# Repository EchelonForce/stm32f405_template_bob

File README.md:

# SMT32F405RG Template/BOB

This is a design for a STM32F405 based breakout board.

This work is licensed under a Creative Commons Attribution-NonCommercial-ShareAlike 4.0 International License. https://creativecommons.org/licenses/by-nc-sa/4.0/

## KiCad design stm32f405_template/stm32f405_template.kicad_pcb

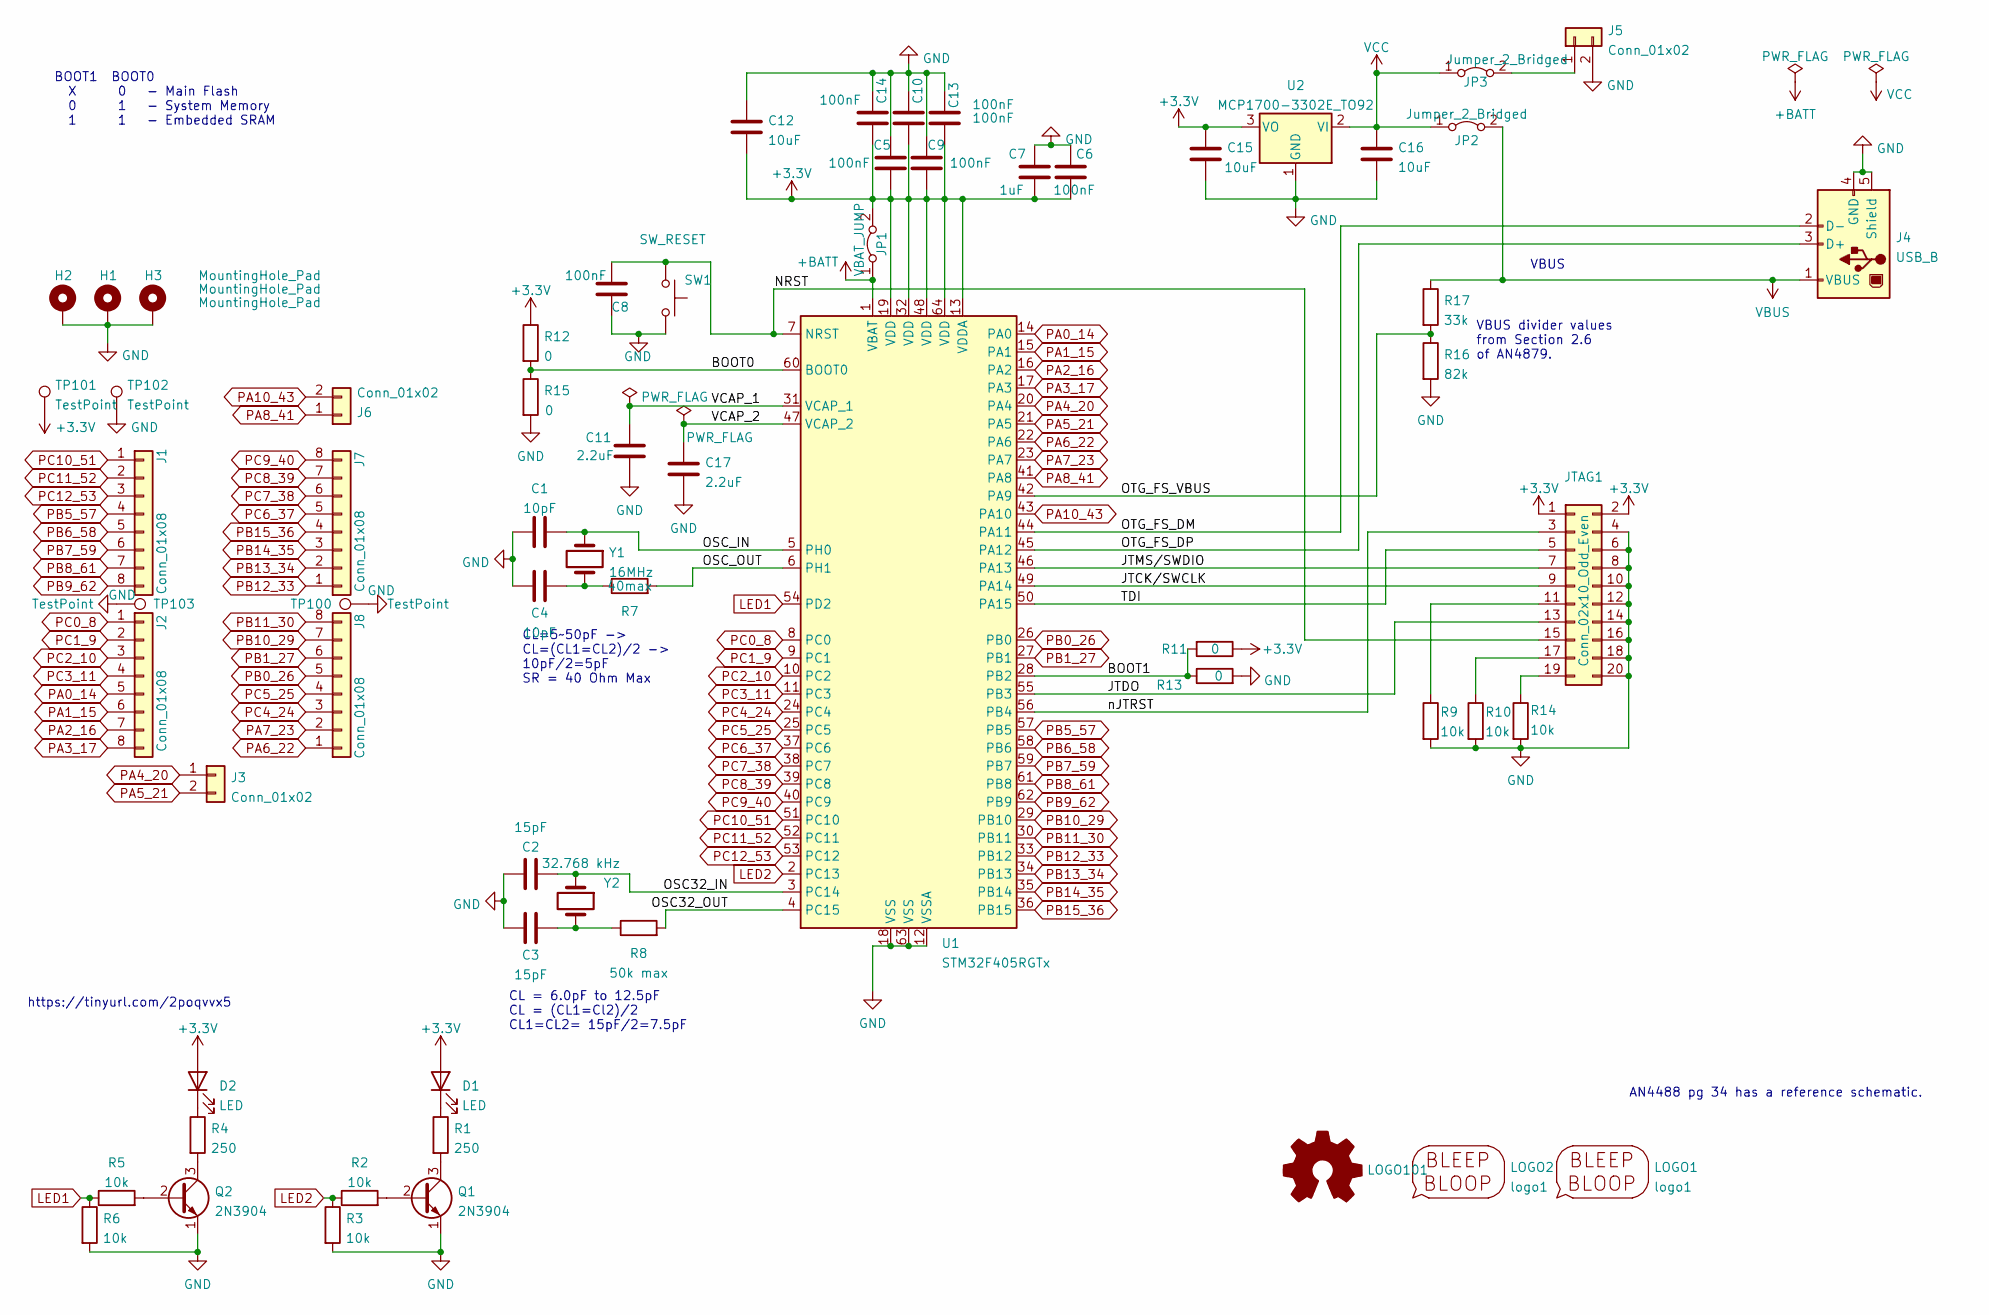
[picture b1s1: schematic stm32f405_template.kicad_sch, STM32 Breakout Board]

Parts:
C1, C4: 10pF; C_1206_3216Metric_Pad1.33x1.80mm_HandSolder
C2, C3: 15pF; C_1206_3216Metric_Pad1.33x1.80mm_HandSolder
C5, C6, C8, C9, C10, C13, C14: 100nF; C_1206_3216Metric_Pad1.33x1.80mm_HandSolder
C7: 1uF; C_1206_3216Metric_Pad1.33x1.80mm_HandSolder
C11, C17: 2.2uF; C_1206_3216Metric_Pad1.33x1.80mm_HandSolder
C12, C15, C16: 10uF; C_Disc_D5.0mm_W2.5mm_P5.00mm
D1, D2: LED; LED_D3.0mm
H1, H2, H3: MountingHole_Pad; MountingHole_3.2mm_M3_DIN965_Pad_TopBottom
J1, J2, J7, J8: Conn_01x08; PinHeader_1x08_P2.54mm_Vertical
J3, J5, J6: Conn_01x02; PinHeader_1x02_P2.54mm_Vertical
J4: USB_B; USB_Mini-B_Lumberg_2486_01_Horizontal
JP1: VBAT_JUMP; SolderJumper-2_P1.3mm_Bridged_Pad1.0x1.5mm
JP2, JP3: Jumper_2_Bridged; SolderJumper-2_P1.3mm_Bridged_RoundedPad1.0x1.5mm
JTAG1: Conn_02x10_Odd_Even; IDC-Header_2x10_P2.54mm_Vertical
LOGO1: logo1; OSHW-Symbol_6.7x6mm_SilkScreen
LOGO2: logo1; Logo1
LOGO101: Logo_Open_Hardware_Small; OSHW-Symbol_6.7x6mm_SilkScreen
Q1, Q2: 2N3904; TO-92_Inline_Wide
R1, R4: 250; R_1206_3216Metric_Pad1.30x1.75mm_HandSolder
R2, R3, R5, R6, R9, R10, R14: 10k; R_1206_3216Metric_Pad1.30x1.75mm_HandSolder
R7: 40max; R_1206_3216Metric_Pad1.30x1.75mm_HandSolder
R8: 50k max; R_1206_3216Metric_Pad1.30x1.75mm_HandSolder
R11, R12, R13, R15: 0; R_1206_3216Metric_Pad1.30x1.75mm_HandSolder
R16: 82k; R_1206_3216Metric_Pad1.30x1.75mm_HandSolder
R17: 33k; R_1206_3216Metric_Pad1.30x1.75mm_HandSolder
SW1: SW_RESET; SW_PUSH_6mm_H5mm
TP100, TP102, TP103: TestPoint; TestPoint_THTPad_1.5x1.5mm_Drill0.7mm
TP101: TestPoint; TestPoint_THTPad_D1.5mm_Drill0.7mm
U1: STM32F405RGTx; LQFP-64_10x10mm_P0.5mm
U2: MCP1700-3302E_TO92; TO-92_Inline_Wide
Y1: 16MHz; Crystal_HC49-4H_Vertical
Y2: 32.768 kHz; Crystal_C38-LF_D3.0mm_L8.0mm_Horizontal

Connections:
+3.3V: C5.1, C6.1, C7.2, C9.1, C10.1, C12.2, C13.1, C14.1, C15.1, D1.2 (A), D2.2 (A), JP1.2 (B), JTAG1.1, JTAG1.2, R11.1, R12.1, TP101.1, U1.13 (VDDA), U1.19 (VDD), U1.32 (VDD), U1.48 (VDD), U1.64 (VDD), U2.3 (VO)
+BATT: JP1.1 (A), U1.1 (VBAT)
/BOOT0: R12.2, R15.1, U1.60 (BOOT0)
/BOOT1: R11.2, R13.1, U1.28 (PB2)
/JTCK/SWCLK: JTAG1.9, U1.49 (PA14)
/JTDO: JTAG1.13, U1.55 (PB3)
/JTMS/SWDIO: JTAG1.7, U1.46 (PA13)
/NRST: C8.1, JTAG1.15, SW1.1, U1.7 (NRST)
/OSC32_IN: C2.2, U1.3 (PC14), Y2.1
/OSC32_OUT: R8.2, U1.4 (PC15)
/OSC_IN: C1.2, U1.5 (PH0), Y1.1
/OSC_OUT: R7.2, U1.6 (PH1)
/OTG_FS_DM: J4.2 (D-), U1.44 (PA11)
/OTG_FS_DP: J4.3 (D+), U1.45 (PA12)
/OTG_FS_VBUS: R16.1, R17.2, U1.42 (PA9)
/TDI: JTAG1.5, U1.50 (PA15)
/VCAP_1: C11.1, U1.31 (VCAP_1)
/VCAP_2: C17.1, U1.47 (VCAP_2)
/nJTRST: JTAG1.3, U1.56 (PB4)
GND: C1.1, C2.1, C3.1, C4.1, C5.2, C6.2, C7.1, C8.2, C9.2, C10.2, C11.2, C12.1, C13.2, C14.2, C15.2, C16.2, C17.2, H1.1, H2.1, H3.1, J4.4 (GND), J4.5 (Shield), J5.2, JTAG1.4, JTAG1.6, JTAG1.8, JTAG1.10, JTAG1.12, JTAG1.14, JTAG1.16, JTAG1.18, JTAG1.20, Q1.1 (E), Q2.1 (E), R3.2, R6.2, R9.2, R10.2, R13.2, R14.2, R15.2, R16.2, SW1.2, TP100.1, TP102.1, TP103.1, U1.12 (VSSA), U1.18 (VSS), U1.63 (VSS), U2.1 (GND)
LED1: R5.1, R6.1, U1.54 (PD2)
LED2: R2.1, R3.1, U1.2 (PC13)
unnamed: C3.2, R8.1, Y2.2
unnamed: C4.2, R7.1, Y1.2
unnamed: D1.1 (K), R1.1
unnamed: D2.1 (K), R4.1
unnamed: J5.1, JP3.2 (B)
unnamed: JTAG1.11, R9.1
unnamed: JTAG1.17, R10.1
unnamed: JTAG1.19, R14.1
unnamed: Q1.2 (B), R2.2
unnamed: Q1.3 (C), R1.2
unnamed: Q2.2 (B), R5.2
unnamed: Q2.3 (C), R4.2
PA0_14: J2.5, U1.14 (PA0)
PA1_15: J2.6, U1.15 (PA1)
PA2_16: J2.7, U1.16 (PA2)
PA3_17: J2.8, U1.17 (PA3)
PA4_20: J3.1, U1.20 (PA4)
PA5_21: J3.2, U1.21 (PA5)
PA6_22: J8.1, U1.22 (PA6)
PA7_23: J8.2, U1.23 (PA7)
PA8_41: J6.1, U1.41 (PA8)
PA10_43: J6.2, U1.43 (PA10)
PB0_26: J8.5, U1.26 (PB0)
PB1_27: J8.6, U1.27 (PB1)
PB5_57: J1.4, U1.57 (PB5)
PB6_58: J1.5, U1.58 (PB6)
PB7_59: J1.6, U1.59 (PB7)
PB8_61: J1.7, U1.61 (PB8)
PB9_62: J1.8, U1.62 (PB9)
PB10_29: J8.7, U1.29 (PB10)
PB11_30: J8.8, U1.30 (PB11)
PB12_33: J7.1, U1.33 (PB12)
PB13_34: J7.2, U1.34 (PB13)
PB14_35: J7.3, U1.35 (PB14)
PB15_36: J7.4, U1.36 (PB15)
PC0_8: J2.1, U1.8 (PC0)
PC1_9: J2.2, U1.9 (PC1)
PC2_10: J2.3, U1.10 (PC2)
PC3_11: J2.4, U1.11 (PC3)
PC4_24: J8.3, U1.24 (PC4)
PC5_25: J8.4, U1.25 (PC5)
PC6_37: J7.5, U1.37 (PC6)
PC7_38: J7.6, U1.38 (PC7)
PC8_39: J7.7, U1.39 (PC8)
PC9_40: J7.8, U1.40 (PC9)
PC10_51: J1.1, U1.51 (PC10)
PC11_52: J1.2, U1.52 (PC11)
PC12_53: J1.3, U1.53 (PC12)
VBUS: J4.1 (VBUS), JP2.2 (B), R17.1
VCC: C16.1, JP2.1 (A), JP3.1 (A), U2.2 (VI)

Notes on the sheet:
AN4488 pg 34 has a reference schematic.
BOOT1 BOOT0 X 0 - Main Flash 0 1 - System Memory 1 1 - Embedded SRAM
https://tinyurl.com/2poqvvx5
CL = 6.0pF to 12.5pF CL = (CL1=Cl2)/2 CL1=CL2= 15pF/2=7.5pF
VBUS divider values from Section 2.6 of AN4879.
VBUS
CL=5~50pF -> CL=(CL1=CL2)/2 -> 10pF/2=5pF SR = 40 Ohm Max

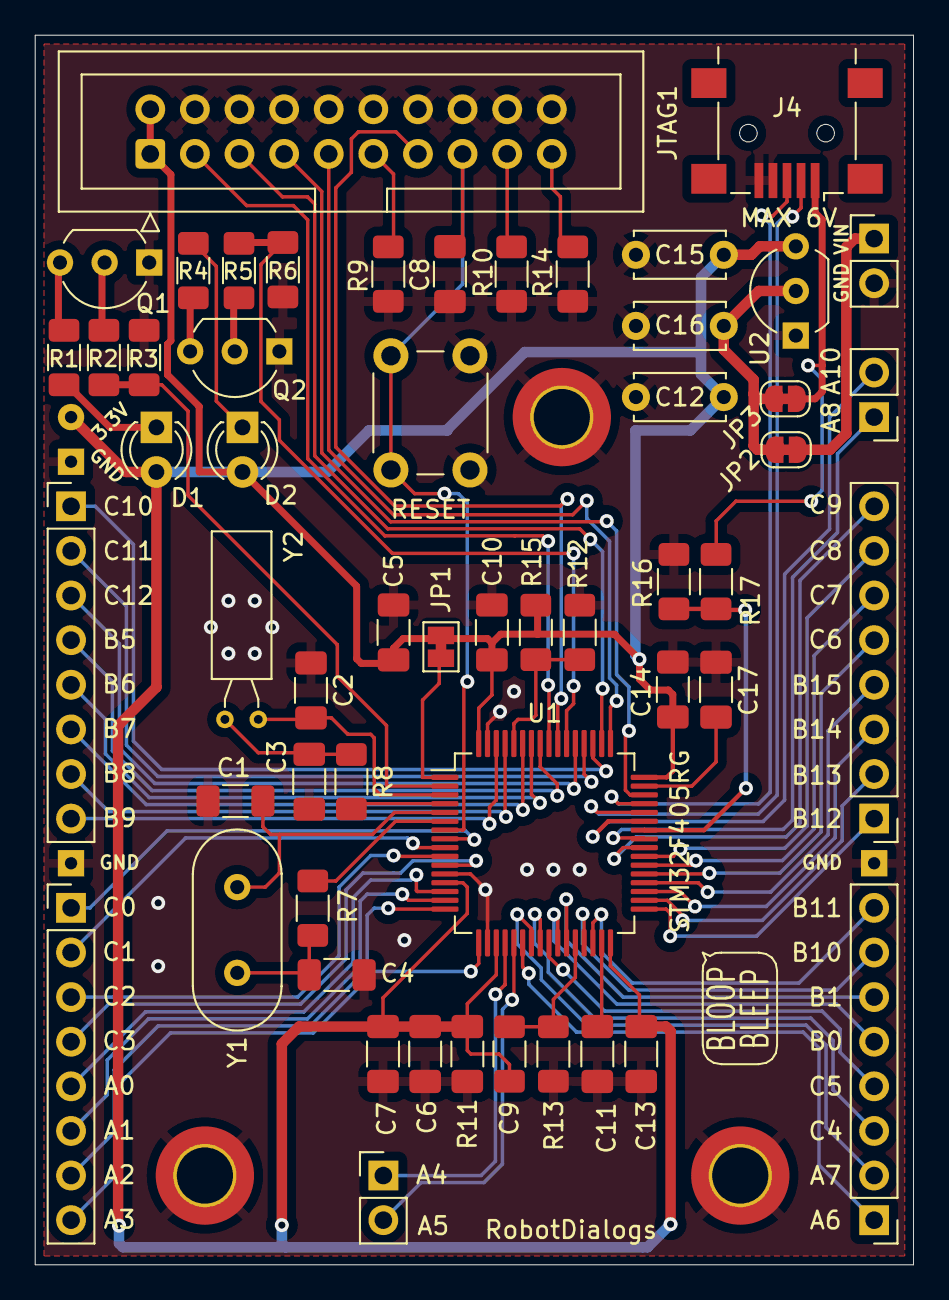
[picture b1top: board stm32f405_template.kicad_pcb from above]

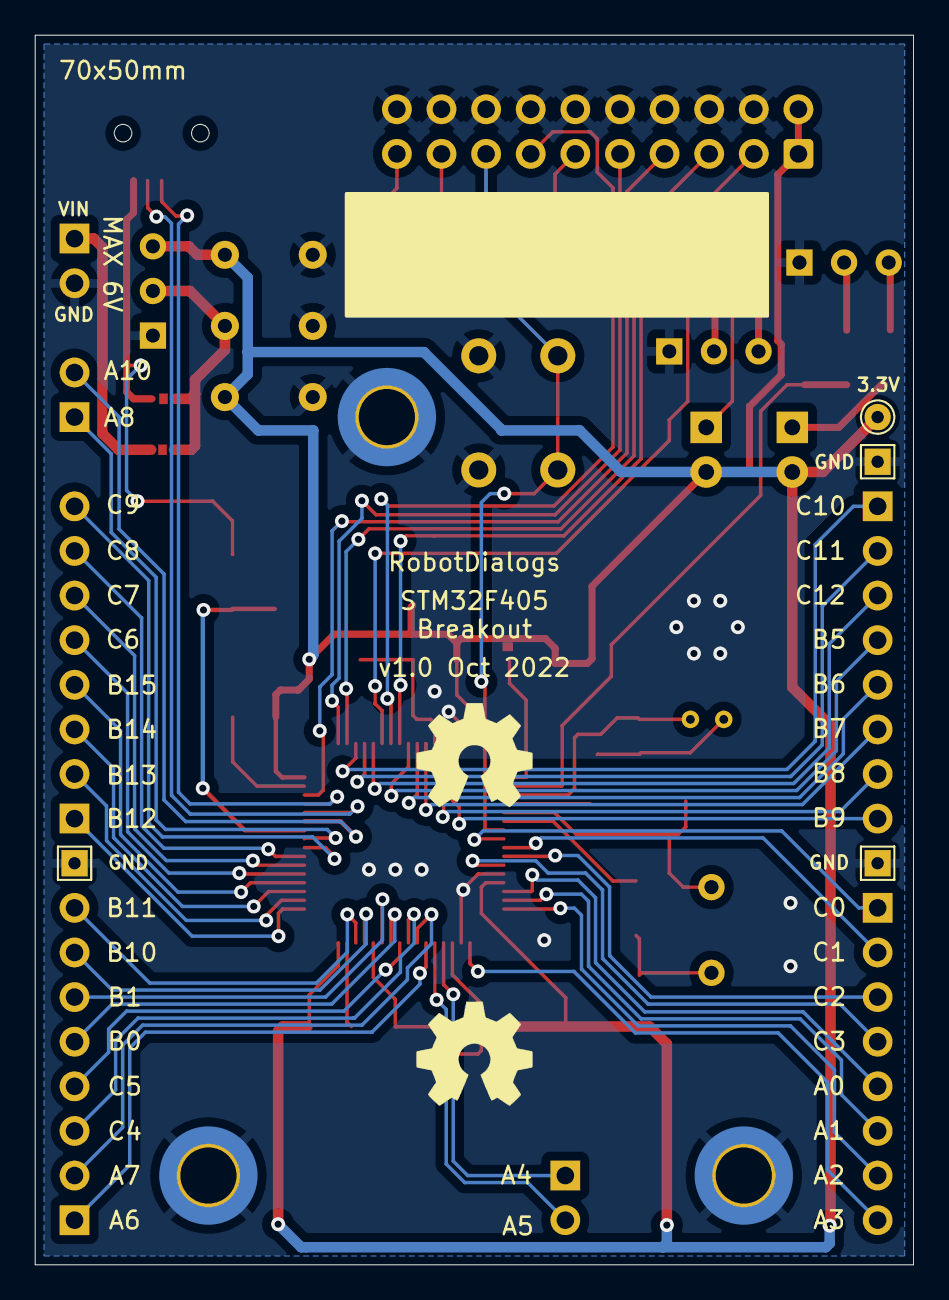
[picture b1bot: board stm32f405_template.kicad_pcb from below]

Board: 2 copper layers, 50.0 x 70.0 mm, 65 parts (6 on the bottom side), 72 nets.

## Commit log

2022-10-04 Initial commit with .gitignore
2022-10-04 Initial schematic and pcb layout and routing draft
2022-10-04 Geographic re-annotate and cleanup
2022-10-04 Silkscreen cleanup
2022-10-10 Tidied silkscreen and some routing cleanup
2022-10-10 panelized v1
2023-01-16 v1 schematic pdf with some assembly updates and notes
